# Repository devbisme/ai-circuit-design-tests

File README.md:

# ai-circuit-design-tests

There are now many [AI tools](https://devbisme.github.io/RepoRecon/?topic=kicad_ai&filter=&sort=pushed:desc) that claim to automate KiCad.
Some may work, many may not; it's hard to tell since example designs are either non-existent, show only partial results, or
are very simple (e.g. resistor dividers).

I'm going to try some of these AI tools to see how they perform.
This repo is the test bench. Each top-level subdirectory holds the artifacts of one tool
being exercised on a real design problem, plus an evaluation of what came out and what it
cost.

The tools that were tested fall into the following classes:

- **Generators** take a design prompt and produce a design: specs, BOM, schematics,
  netlists, and sometimes a board.
- **Analyzers** take an existing KiCad design and produce a report: design review findings,
  ERC/DRC/DFM checks, simulations, sourcing, etc. They don't create a design of their own,
  so they are run on a design produced by one of the generators tested here.
- **Hybrids** can both generate and analyze designs. They are tested in both roles: one run
  analyzes an existing design, and another creates a design from a prompt.

Because of this, the results and the directory layout differ between the classes.
A generator's output is judged by whether the design is correct and complete; an analyzer's
output is judged by whether its findings are real, relevant, and not missing anything important.

Note that I have not validated any of these designs for correctness.
I will report the results of my validation in each tool's directory when I'm done.
Please feel free to report any of your own evaluations here as an issue on this repo.

**If you are interested in trying any of these tools,**
the most important files to read are:

* `setup.md` which describes how to install the tool,

* `claude_transcript.txt` (in each run directory) which shows the interactions between the
  user and Claude when using the tool.

For a quick look at what a run produced, start with its `executive_summary.md`.

## Tools tested

| Directory | Tool | Class |
|---|---|---|
| [`skidl-skills-tests/`](skidl-skills-tests/) | [skidl-skills](https://github.com/devbisme/skidl-skills) | Generator |
| [`konnect-tests/`](konnect-tests/) | [Konnect](https://github.com/mixelpixx/Konnect) | Hybrid |
| [`copperhead-tests/`](copperhead-tests/) | [Copperhead](https://github.com/copperheadhq/copperhead) | Generator |
| [`kicad-happy-tests/`](kicad-happy-tests/) | [kicad-happy](https://github.com/aklofas/kicad-happy) | Analyzer |
| [`kicad-mcp-server-tests/`](kicad-mcp-server-tests/) | [kicad-mcp-server](https://github.com/Seeed-Studio/kicad-mcp-server) | Hybrid |
| [`kicad-mcp-pro-tests/`](kicad-mcp-pro-tests/) | [kicad-mcp-pro](https://github.com/oaslananka/kicad-mcp-pro) | Hybrid |
| [`eda-agent-tests/`](eda-agent-tests/) | [eda-agent](https://github.com/salitronic/eda-agent) | Hybrid |
| [`kicad-ai-assistant-tests/`](kicad-ai-assistant-tests/) | [KiCad-AI-Assistant](https://github.com/paul356/KiCad-AI-Assistant) | Hybrid |
| [`kicad-harness-tests/`](kicad-harness-tests/) | [kicad-harness](https://github.com/zxkmm/kicad-harness) | Hybrid |
| [`boardforge-tests/`](boardforge-tests/) | [boardforge](https://github.com/devbisme/boardforge) | Generator |
| [`null-tests/`](null-tests/) | None: Claude Code (Opus 5.5) with no KiCad-specific MCP servers, skills or plugins; a baseline | Hybrid |

Each generator's `README.md` describes the tool, why it was chosen, the prompt(s) it was given,
a cross-run comparison, and an evaluation of cost, runtime and quality of results.
Each analyzer's directory holds a copy of the design it analyzed (and notes where it came from),
the reports the tool produced, and an evaluation of the findings, cost and runtime.
A hybrid's directory has one of each kind of run.

## Comparable runs

Two sets of runs share their inputs, so their results can be compared across tools.

**Same design prompt.** These runs got the dual-ADC requirements prompt (dual-channel,
±10 V, 10 MS/s, 12-bit, ≥0.1 s of capture, USB 2.0). Each was told to start from a blank
slate.

| Run | Tool's role | Reached (as reported by the session) | Equiv. API cost |
|---|---|---|---|
| [Konnect 2](konnect-tests/dual-adc-usb-2/) | Design tool | Routed 4-layer board, DRC clean | $61.12 |
| [kicad-mcp-server 2](kicad-mcp-server-tests/dual-adc-usb-2/) | Design tool, gaps filled by scripts | Routed 4-layer board, 4 DRC errors (stock USB-C footprint) | $16.93 |
| [kicad-happy 2](kicad-happy-tests/dual-adc-usb-2/) | Reviewer; Claude built the design with SKiDL and scripts | Routed 4-layer board, 0 ERC/DRC errors | $29.37 |
| [kicad-mcp-pro 2](kicad-mcp-pro-tests/dual-adc-usb-2/) | Design tool, gaps filled by scripts | Routed 4-layer board, 0 ERC/DRC errors | $19.42 |
| [eda-agent 2](eda-agent-tests/dual-adc-usb-2/) | Design tool (KiCad backend), gaps filled by scripts | Routed 4-layer board, 0 ERC/DRC errors | $18.47 |
| [KiCad-AI-Assistant 2](kicad-ai-assistant-tests/dual-adc-usb-2/) | Design tool (kcaa MCP server), gaps filled by scripts | Routed 4-layer board, 0 ERC/DRC errors | $19.38 |
| [kicad-harness 2](kicad-harness-tests/generate-1/) | Checks, lookups and renders (`kh` CLI); Claude's scripts wrote the schematic, placed and finished routing | Routed 4-layer board, 0 ERC/DRC errors | $10.87 |
| [null test 2](null-tests/generate-1/) | No tool (baseline): Claude used SKiDL and schematizer for the schematic, its own `pcbnew` scripts and Freerouting for the board | Routed 4-layer board, 0 ERC/DRC errors; signals routed through the In1 GND plane | $11.16 |
| [boardforge 1](boardforge-tests/generate-1/) | Design pipeline: `/new-circuit` agents wrote the SKiDL design, the `boardforge` CLI made the schematic, placed, routed and wrote fab files | Routed 4-layer board, 0 ERC/DRC errors, review and release gates PASS; CPL dropped 80 parts (tool bug, fixed by hand) | $23.89 |

These nine runs used the prompt with an added line giving the KiCad 10 executable's path.
The version without that line was used for SKiDL Skills runs 5–9, Konnect run 1 and
Copperhead run 1.

**Same input design.** These runs analyzed the KiCad project from Konnect run 2.

| Run | Equiv. API cost |
|---|---|
| [kicad-happy 1](kicad-happy-tests/dual-adc-usb-1/) | $1.92 |
| [kicad-mcp-server 1](kicad-mcp-server-tests/dual-adc-usb-1/) | $2.05 |
| [kicad-mcp-pro 1](kicad-mcp-pro-tests/dual-adc-usb-1/) | $2.24 |
| [eda-agent 1](eda-agent-tests/dual-adc-usb-1/) | $3.43 |
| [KiCad-AI-Assistant 1](kicad-ai-assistant-tests/dual-adc-usb-1/) | $3.71 |
| [kicad-harness 1](kicad-harness-tests/analyze-1/) | $3.02 |
| [null test 1](null-tests/analyze-1/) | $1.91 |

The prompts differed between these runs, so they did not ask for exactly the same things.
Each tool's `README.md` lists its prompts and findings.

None of these designs or findings has been validated yet.

## Layout

This is the layout for generators. Analyzers follow it loosely: the KiCad files in their
directories are inputs copied from a generator's run, not outputs, and the main output is
the analysis report.

```
ai-circuit-design-tests/
├── README.md                 <- this file
└── <tool-name>-tests/        <- one directory per AI tool under test
    ├── README.md             <- the tool, the design prompt, cross-run comparison, evaluation
    ├── setup.md              <- how the tool was installed and configured
    └── <design>-<run#>/      <- one directory per run
        ├── README.md         <- (some runs) what was run, what came out, evaluation, cost
        ├── *-prompt.txt          <- the verbatim prompt given to the tool
        ├── claude_transcript.txt <- transcript of interactions between the user and Claude
        ├── claude_cost.txt       <- token usage and equivalent API cost
        ├── executive_summary.md  <- overall description of the design process, results, risks.
        └── ...                   <- everything the tool produced
```

One run per directory, never overwritten. Runs are numbered so a prompt change or a tool
change can be compared against the previous attempt on the same design. Where possible,
different tools are given the same design prompt so their results can be compared.

## What each run should capture

- The verbatim prompt (`*-prompt.txt`).
- Everything the tool wrote — specs, architecture docs, BOM, datasheets, code, ERC/DRC logs,
  netlists, schematics, boards — left where the tool put it.
- The session transcript (`claude_transcript.txt`, via `/export`), when the tool is interactive.
- Cost. `claude_cost.txt` holds token counts and the equivalent first-party API price. It
  comes from `session_cost.py`, which sums usage from the main transcript **and** the
  subagent transcripts; the main file alone misses most of the spend. Save it at the end of
  the session, before doing any unrelated work in the same session, or the total will
  include that work too.

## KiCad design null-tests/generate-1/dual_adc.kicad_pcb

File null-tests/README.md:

# Null test — tests

## Tool under test

None. This is a **null test**: Claude Code with Claude Opus 5.5 and no KiCad-specific MCP
server, skill, plugin, subagent or memory. It is the baseline for the other tools in this
repo: their results can be read against what Claude does with only its built-in tools.

What it has to work with:

- Claude Code's built-in tools: Bash, Read, Write, Edit, web search and fetch.
- KiCad 10's own programs: `kicad-cli` (ERC, DRC, netlist, Gerber, drill, BOM, position,
  PDF/SVG export) and the `pcbnew` Python module in KiCad 10's bundled Python 3.11.
- Whatever else it finds on the machine. That includes KiCad-specific Python packages and
  CLIs that were not removed (`skidl`, `schematizer`, `kipart`, `kinet2pcb`, `kicad-skip`; see [`setup.md`](setup.md)).

Claude can both review and create designs, so this is tested as a **hybrid**, like
[kicad-harness](../kicad-harness-tests/) and [KiCad-AI-Assistant](../kicad-ai-assistant-tests/).
Setup, including what has to be turned off before each run, is in [`setup.md`](setup.md).

- **Version:** n/a (no tool).
- **Model:** Claude Opus 5.5 on a Claude Pro plan (both runs).
- **Claude Code version:** v2.1.301 (both runs).
- **Backend:** KiCad 10.0.4 (`~/bin/kicad10-root`: `kicad-cli` and the bundled Python 3.11
  `pcbnew`).

## Why this tool

*Draft:* every other tool here is judged by what it produced, but not against what Claude
would have produced without it. The null test supplies that comparison: the same two prompts,
the same model and the same KiCad 10, with none of the tools.

## Runs

| Run | What it tests | Prompts | Outcome | Equiv. API cost | Time |
|---|---|---|---|---|---|
| [`analyze-1`](analyze-1/) | **Analysis** and JLCPCB fab outputs for an existing design (Konnect run 2) | 1 (multi-part, [`analysis_prompt.txt`](analyze-1/analysis_prompt.txt)) | ERC 0 errors, DRC 0 errors; 15 ranked findings; Gerbers, BOM, CPL, PNG. Its top finding (clamp diodes miswired) is probably a false positive | $1.91 | ~6 min |
| [`generate-1`](generate-1/) | A **full design** from the dual-ADC requirements | 1, plus 1 "are you done?" while Freerouting ran ([`design_prompt.txt`](generate-1/design_prompt.txt)) | 10-sub-sheet schematic and routed 4-layer board. ERC 0 errors, DRC 0 errors / 0 unconnected / 0 parity. Signals routed through the In1 GND plane | $11.16 | ~2 h 42 min wall clock (~1 h 17 min of Claude working time) |

Each run directory has an `executive_summary.md`; start there. Costs are the equivalent
first-party API price of the tokens used (`claude_cost.txt`), not what the Pro subscription
billed. The findings in both runs have not yet been validated by hand.

### analyze-1: analyzer on an existing design

The input is the KiCad project produced by
[Konnect run 2](../konnect-tests/dual-adc-usb-2/): a 4-layer, 140 × 90 mm dual-channel 12-bit,
10 MS/s ADC board with a USB 2.0 interface (LTC2290 ADC, iCE40HX4K FPGA, SDRAM, FT2232H).
The `.kicad_*` files are unchanged copies. The other tools' analysis runs used the same
design.

Prompt: `do what aanalysis_prompt.txt says to do.` (typo as typed;
[`analysis_prompt.txt`](analyze-1/analysis_prompt.txt) asks for a design review, JLCPCB
Gerbers, BOM and CPL, a dark-gray PCB PNG and an executive summary.)

Quick look:

- **Checks:** `kicad-cli` ERC gave 0 errors, 155 library-mismatch warnings and 2 benign
  pin-type warnings. DRC with schematic parity gave 0 errors and 0 unconnected; the warnings
  are library mismatches and silkscreen.
- **Review method:** a netlist export and a per-IC pin-to-net dump (`out/pinmap.txt`) checked
  against datasheet knowledge, plus a script that parsed the `.kicad_pcb` for stackup, plane
  fills, track and via sizes and decap-to-pin distances (`out/pcbstat.txt`). **No datasheets
  were fetched**; part-behaviour claims are from memory and labelled *(datasheet recall)*.
- **Findings (15, ranked High/Medium/Low):**
  - High: BAV199DW input clamps wired so they do nothing; decoupling caps 6–22 mm from their
    pins on the ADC, FPGA, SDRAM, FT2232H and charge pump; the 10 MHz oscillator runs from
    the PWREN#-gated +3V0 rail, so the FPGA has no clock until USB enumerates.
  - Medium: FT2232H channel B (flash/FPGA programming) unusable while channel A is in sync
    FIFO; USB D+/D− not impedance-controlled; the unpowered ADC is back-powered through its
    outputs; the LM27762 charge pump sits between the two AFE channels; likely over the USB
    unconfigured/suspend current limits.
  - Low: single-pole anti-alias filter, shared ADC OVDD/VDD rail, no vias in the ADA4817
    pads, unprotected header GPIO, BNC overhang, silkscreen, library/field housekeeping.
  - A list of items that were checked and found correct (divider compensation, full-scale
    range, FDA common mode, regulator setpoints, LTC2290 configuration, FT2232H support
    parts, iCE40 configuration, SDRAM pinout, planes).
- **The clamp finding is probably wrong.** [eda-agent 1](../eda-agent-tests/dual-adc-usb-1/)
  and [KiCad-AI-Assistant 1](../kicad-ai-assistant-tests/dual-adc-usb-1/) downloaded the
  Diodes BAV199DW datasheet (ds30417) and found that KiCad's pin names are misleading but the
  real package clamps correctly. This run read only the KiCad pin names. It did add "verify
  that the symbol's pin numbering matches the real BAV199DW package", but still ranked the
  finding first. Not yet checked by hand.
- **Outputs:** Gerbers and Excellon drill from `kicad-cli` (Protel extensions, zipped), a
  JLCPCB-format BOM (LCSC column empty) and CPL in `fab/`, and `dual_adc_usb_pcb.png` at
  400 dpi on #3a3a3a. Intermediate reports are in `out/`.
- **Didn't read anything outside the run directory**, as far as the transcript shows.

### generate-1: full design

The prompt is [`design_prompt.txt`](generate-1/design_prompt.txt), identical to the one used
for the other tools' design runs (the version with the KiCad 10 path line).

Prompts, in sequence in one session:

```
create the design described in design_prompt.txt
```
```
are you done?
```

The session ended its turn several times while Freerouting ran in the background, and the
router's completion notices re-started it. Once it ended its turn saying it was waiting on a
second routing pass over the routed board; after about 17 minutes, "are you done?" got it to
check. That pass had gone from 4 unrouted to 60, so Claude stopped it and went back to the first pass's board.

Quick look:

- **Design:**
  - Signal path: BNC → 1 MΩ‖20 pF attenuator with its bottom leg on a REF3020 2.048 V
    reference → BAV199 clamps → OPA356 buffer → THS4521 FDA (other input gets a buffered copy
    of the attenuator's rest voltage) → RC → LTC2290. ±10.09 V full scale, ~4.4 MHz
    bandwidth, 2nd-order anti-aliasing.
  - Capture and link: iCE40HX4K-TQ144 with an 8 MB IS42S16400J SDRAM (0.2 s at full rate,
    twice the requirement); FT232H in sync-245 FIFO mode; SPI config flash programmed from a
    2×4 header.
  - Clock: 10 MHz XO on the 3.0 V analog rail, buffered to the ADC and an FPGA global clock
    pin.
  - Power: USB-B, ~260 mA estimated, so USB-C wasn't needed. TPS62160 buck (3.3 V), AP2112
    (1.2 V), LP5907 (4.5 V analog, 3.0 V ADC/clock). Single supply; no negative rail.
  - The ten decisions (options → choice) are in the executive summary.
- **Schematic:** written in SKiDL (`dual_adc.py`) and drawn by schematizer as a root plus 10
  sub-sheets.
  - The `kicad-cli` netlist of the drawn schematic matches the SKiDL netlist
    (`compare_nets.py`, 0 differing nets). That check caught a schematizer bug that drew a
    PLL-filter R on top of its C and shorted +1V2 to GND.
  - KiCad ERC: 0 errors, 435 warnings (off-grid wire ends, library-copy mismatches, 2
    intentional flash WP/HOLD ties).
- **PCB:** 140 × 95 mm, 4 layers (In1 GND plane), 182 footprints, 339 vias.
  - Claude's `make_pcb.py` (KiCad 10 `pcbnew`) loaded footprints, assigned nets, did
    rule-based placement, the outline and the In1 plane. `route.py` handled DSN export,
    SES import, pours and copying symbol fields onto footprints.
  - Freerouting 2.4.1 took four full runs (10–30 min each). Run 3 left 0 unrouted and is the
    delivered board. Run 4, with In1 reserved for GND, left 4 signals and ~19 GND pads
    unconnected and was rejected.
  - DRC (KiCad 10, with schematic parity): 0 errors, 0 unconnected, 0 parity, 30 warnings.
    Track and hole minimums were relaxed to 0.10 mm / 0.25 mm for router neck-downs and the
    buck's thermal vias.
- **Not ready for fab:**
  - Freerouting put 81 nets (~1.7 m of track) on the In1 GND plane, including under the
    ADC. The summary calls this the biggest layout weakness.
  - USB D+/D− not routed as a 90 Ω pair; ~260 mA draw before enumeration (limit 100 mA);
    fixed (not trimmable) attenuator compensation.
  - No datasheets were re-read; LTC2290, FT232H, THS4521, iCE40, TPS62160 and REF3020
    details are from memory and labelled that way. Not simulated.
  - No Gerbers or drill files (the prompt didn't ask for them). No FPGA gateware or host
    software.
- **Problems hit:** schematizer crashed on footprint-only parts, needed `auto_stub=True` to
  route, and overlapped two parts (above); the OPA356 SOIC symbol's hidden NC pins landed on
  nets; `pcbnew`'s `board.Save()` overwrites `.kicad_pro` with default rules, so
  `write_project.py` re-applies them after every save.

### Was the null test clean?

Not entirely; both points come from the end of the generate-1 transcript and from
`setup.md`.

- **KiCad-specific packages were used.** generate-1 built the schematic with SKiDL and
  schematizer, which `setup.md` left installed. Claude also read schematizer's README and
  source to work around its bugs. analyze-1 used only `kicad-cli` and its own Python.
- **generate-1 read the repo-root README.** Asked afterwards, Claude said it read the root
  `README.md`, including the "Comparable runs" table, and that the table "is why I aimed for
  a routed, DRC-clean 4-layer board instead of stopping at a schematic". It said it chose the
  architecture before opening the README and copied no design details, but couldn't rule out
  an influence on later choices. It read none of the other tools' design files or reports.
  For future runs, moving that table aside or blocking reads above `null-tests/` would close
  this leak.

### Comparison of the two runs, and with the other tools

- **Cost:** analyze-1 ($1.91) is the cheapest of the analysis runs on this design
  ($1.92–$3.71). generate-1 ($11.16) is close to kicad-harness 2 ($10.87), the cheapest of
  the tool-assisted design runs ($10.87–$61.12).
- **Datasheets:** neither run fetched a datasheet. The tools whose runs did (eda-agent and
  KiCad-AI-Assistant in their analysis runs) avoided the clamp false positive. Fetching
  datasheets isn't something those tools add; it is a choice the session made.
- **Gap filling:** generate-1 looks like the tool-assisted design runs from the other side:
  they also ended with Claude-written scripts for placement and routing, plus Freerouting.
  The difference is the schematic, which here came from SKiDL and schematizer rather than
  the tool under test.
- **Same weak spots as the other design runs:** USB pair impedance, unconfigured USB current,
  silkscreen, and part details from memory.

## Layout

```
null-tests/
├── README.md                   <- this file
├── setup.md                    <- what was turned off for the runs, and why
├── analyze-1/                  <- run 1: analysis of the Konnect run-2 design
│   ├── executive_summary.md    <- start here
│   ├── analysis_prompt.txt     <- the prompt (unchanged copy of the repo-root one)
│   ├── CLAUDE.md               <- empty project memory file
│   ├── claude_transcript.txt   <- the session
│   ├── claude_cost.txt         <- token usage and equivalent API cost
│   ├── session_cost.py         <- script that produced claude_cost.txt
│   ├── dual_adc_usb.kicad_pro, .kicad_sch, .kicad_pcb, .kicad_prl, .kicad_dru
│   ├── adc, afe_a, afe_b, fpga, power, usb .kicad_sch
│   ├── dual_adc_usb_pcb.png    <- PCB render on a dark-gray background
│   ├── fab/                    <- Gerber zip, unzipped gerbers, JLCPCB BOM and CPL
│   └── out/                    <- ERC/DRC JSON, netlist, pin map, PCB stats, raw BOM/pos, SVG
└── generate-1/                 <- run 2: full design from the dual-ADC prompt
    ├── executive_summary.md    <- start here
    ├── design_prompt.txt       <- the design prompt
    ├── CLAUDE.md               <- empty project memory file
    ├── claude_transcript.txt   <- the session
    ├── claude_cost.txt         <- token usage and equivalent API cost
    ├── session_cost.py         <- script that produced claude_cost.txt
    ├── dual_adc.py             <- SKiDL description of the circuit (source of truth)
    ├── dual_adc.kicad_pro, .kicad_sch, .kicad_pcb, .kicad_prl
    ├── dual_adc_*.kicad_sch    <- 10 sub-sheets drawn by schematizer
    ├── dual_adc_schematic.pdf, dual_adc_top.png, dual_adc_bom.csv
    ├── dual_adc.net, dual_adc_sch.net  <- SKiDL netlist / netlist of the drawn schematic
    ├── dual_adc.xml, dual_adc.erc, dual_adc.log  <- SKiDL outputs
    ├── erc.rpt, drc.rpt        <- final KiCad 10 ERC/DRC reports
    ├── dual_adc.dsn, dual_adc.ses, freerouting.log  <- Freerouting input/output
    ├── fix_sch.py              <- schematic post-fix (PWR_FLAG footprints)
    ├── compare_nets.py         <- netlist-vs-netlist check
    ├── make_pcb.py             <- footprints, nets, placement, outline, In1 plane
    ├── route.py                <- DSN export, SES import, pours, symbol-field relink
    ├── finish_board.py         <- starved-thermal fixes, board-only holes, zone refill
    └── write_project.py        <- writes .kicad_pro design rules and net classes
```

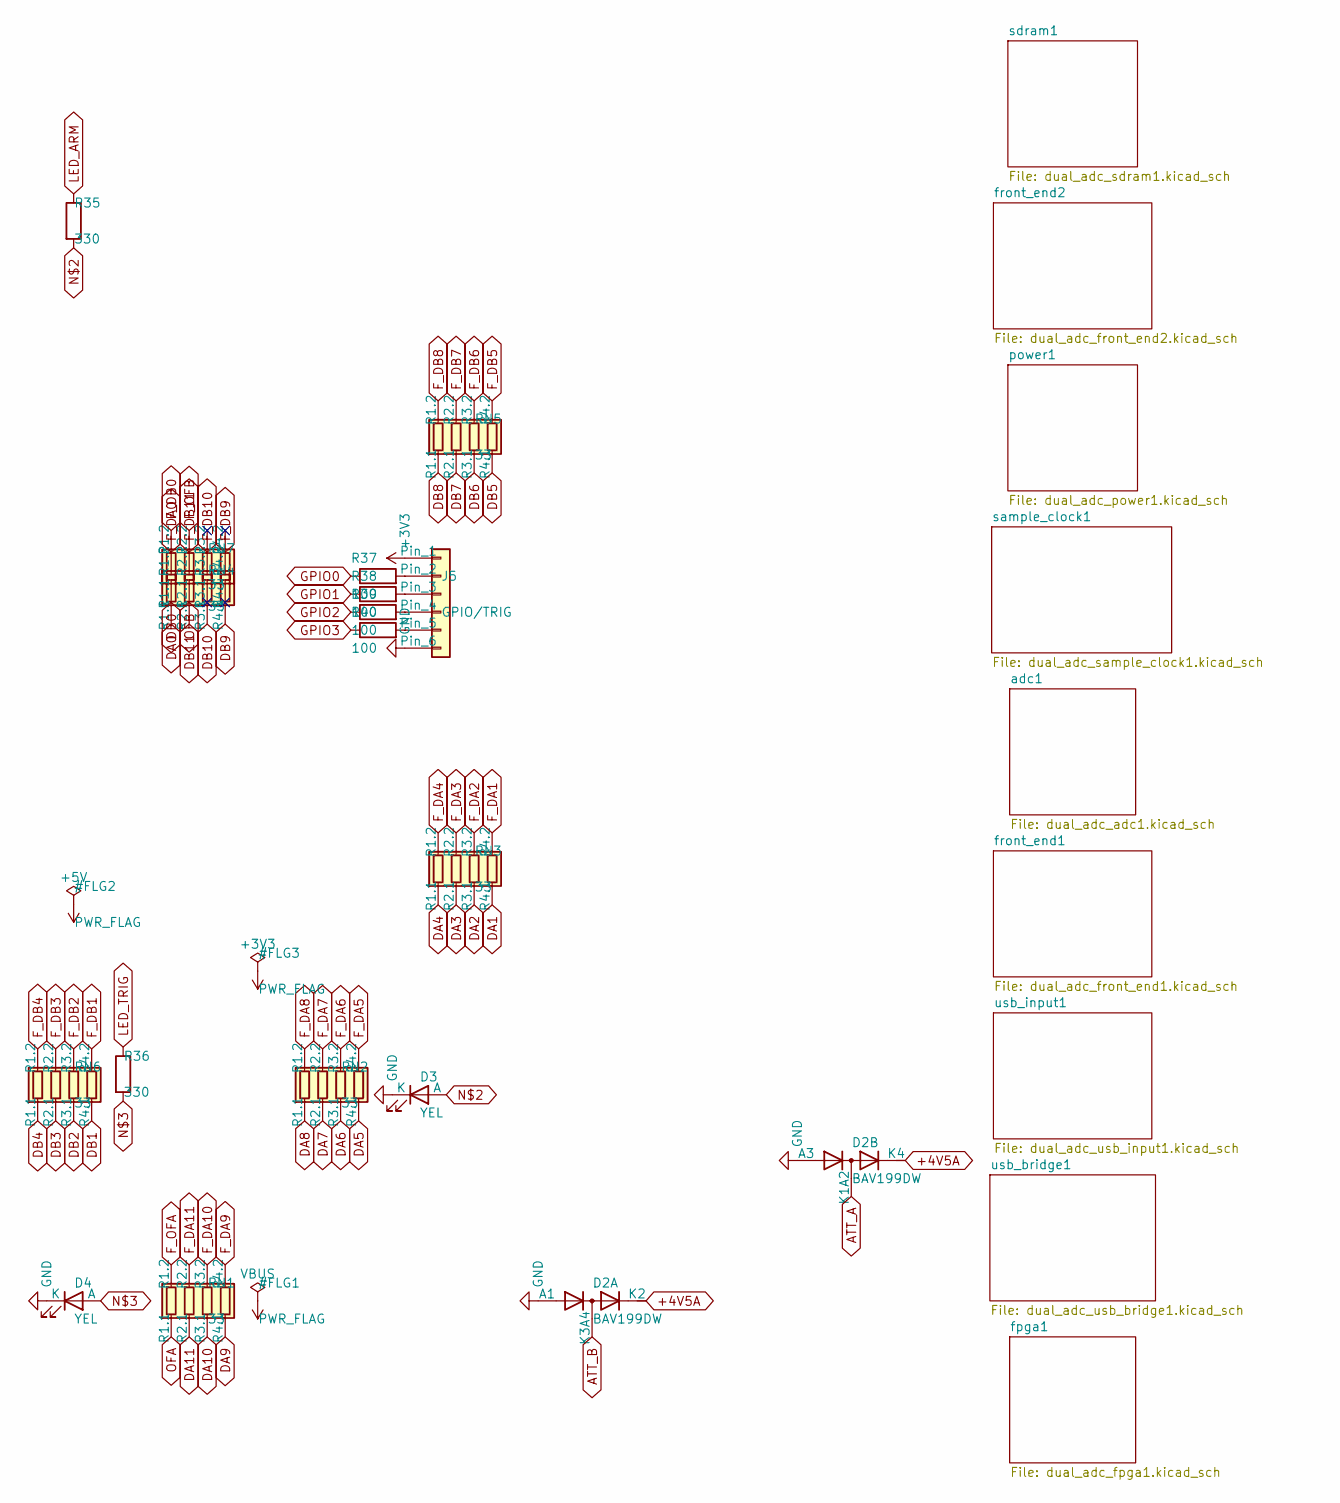
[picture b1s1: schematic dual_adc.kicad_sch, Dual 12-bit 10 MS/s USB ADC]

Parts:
D2: BAV199DW; SOT-363_SC-70-6
D3, D4: YEL; LED_0603_1608Metric
J5: GPIO/TRIG; PinHeader_1x06_P2.54mm_Vertical
R35, R36: 330; R_0603_1608Metric
R37, R38, R39, R40: 100; R_0603_1608Metric
RN1, RN2, RN3, RN4, RN5, RN6, RN7: 33; R_Array_Convex_4x0603

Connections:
+3V3: J5.1; also elsewhere on the board
+4V5A: D2.2 (K2), D2.5 (K4); also elsewhere on the board
ATT_A: D2.3 (K1A2); also elsewhere on the board
ATT_B: D2.6 (K3A4); also elsewhere on the board
DA0: RN4.1 (R1.1); also elsewhere on the board
DA1: RN3.4 (R4.1); also elsewhere on the board
DA2: RN3.3 (R3.1); also elsewhere on the board
DA3: RN3.2 (R2.1); also elsewhere on the board
DA4: RN3.1 (R1.1); also elsewhere on the board
DA5: RN2.4 (R4.1); also elsewhere on the board
DA6: RN2.3 (R3.1); also elsewhere on the board
DA7: RN2.2 (R2.1); also elsewhere on the board
DA8: RN2.1 (R1.1); also elsewhere on the board
DA9: RN1.4 (R4.1); also elsewhere on the board
DA10: RN1.3 (R3.1); also elsewhere on the board
DA11: RN1.2 (R2.1); also elsewhere on the board
DB0: RN7.1 (R1.1); also elsewhere on the board
DB1: RN6.4 (R4.1); also elsewhere on the board
DB2: RN6.3 (R3.1); also elsewhere on the board
DB3: RN6.2 (R2.1); also elsewhere on the board
DB4: RN6.1 (R1.1); also elsewhere on the board
DB5: RN5.4 (R4.1); also elsewhere on the board
DB6: RN5.3 (R3.1); also elsewhere on the board
DB7: RN5.2 (R2.1); also elsewhere on the board
DB8: RN5.1 (R1.1); also elsewhere on the board
DB9: RN4.4 (R4.1); also elsewhere on the board
DB10: RN4.3 (R3.1); also elsewhere on the board
DB11: RN4.2 (R2.1); also elsewhere on the board
F_DA0: RN4.8 (R1.2); also elsewhere on the board
F_DA1: RN3.5 (R4.2); also elsewhere on the board
F_DA2: RN3.6 (R3.2); also elsewhere on the board
F_DA3: RN3.7 (R2.2); also elsewhere on the board
F_DA4: RN3.8 (R1.2); also elsewhere on the board
F_DA5: RN2.5 (R4.2); also elsewhere on the board
F_DA6: RN2.6 (R3.2); also elsewhere on the board
F_DA7: RN2.7 (R2.2); also elsewhere on the board
F_DA8: RN2.8 (R1.2); also elsewhere on the board
F_DA9: RN1.5 (R4.2); also elsewhere on the board
F_DA10: RN1.6 (R3.2); also elsewhere on the board
F_DA11: RN1.7 (R2.2); also elsewhere on the board
F_DB0: RN7.8 (R1.2); also elsewhere on the board
F_DB1: RN6.5 (R4.2); also elsewhere on the board
F_DB2: RN6.6 (R3.2); also elsewhere on the board
F_DB3: RN6.7 (R2.2); also elsewhere on the board
F_DB4: RN6.8 (R1.2); also elsewhere on the board
F_DB5: RN5.5 (R4.2); also elsewhere on the board
F_DB6: RN5.6 (R3.2); also elsewhere on the board
F_DB7: RN5.7 (R2.2); also elsewhere on the board
F_DB8: RN5.8 (R1.2); also elsewhere on the board
F_DB9: RN4.5 (R4.2); also elsewhere on the board
F_DB10: RN4.6 (R3.2); also elsewhere on the board
F_DB11: RN4.7 (R2.2); also elsewhere on the board
F_OFA: RN1.8 (R1.2); also elsewhere on the board
F_OFB: RN7.7 (R2.2); also elsewhere on the board
GND: D2.1 (A1), D2.4 (A3), D3.1 (K), D4.1 (K), J5.6; also elsewhere on the board
GPIO0: R37.1; also elsewhere on the board
GPIO1: R38.1; also elsewhere on the board
GPIO2: R39.1; also elsewhere on the board
GPIO3: R40.1; also elsewhere on the board
LED_ARM: R35.1; also elsewhere on the board
LED_TRIG: R36.1; also elsewhere on the board
unnamed: D3.2 (A), R35.2
unnamed: D4.2 (A), R36.2
unnamed: J5.2, R37.2
unnamed: J5.3, R38.2
unnamed: J5.4, R39.2
unnamed: J5.5, R40.2
OFA: RN1.1 (R1.1); also elsewhere on the board
OFB: RN7.2 (R2.1); also elsewhere on the board

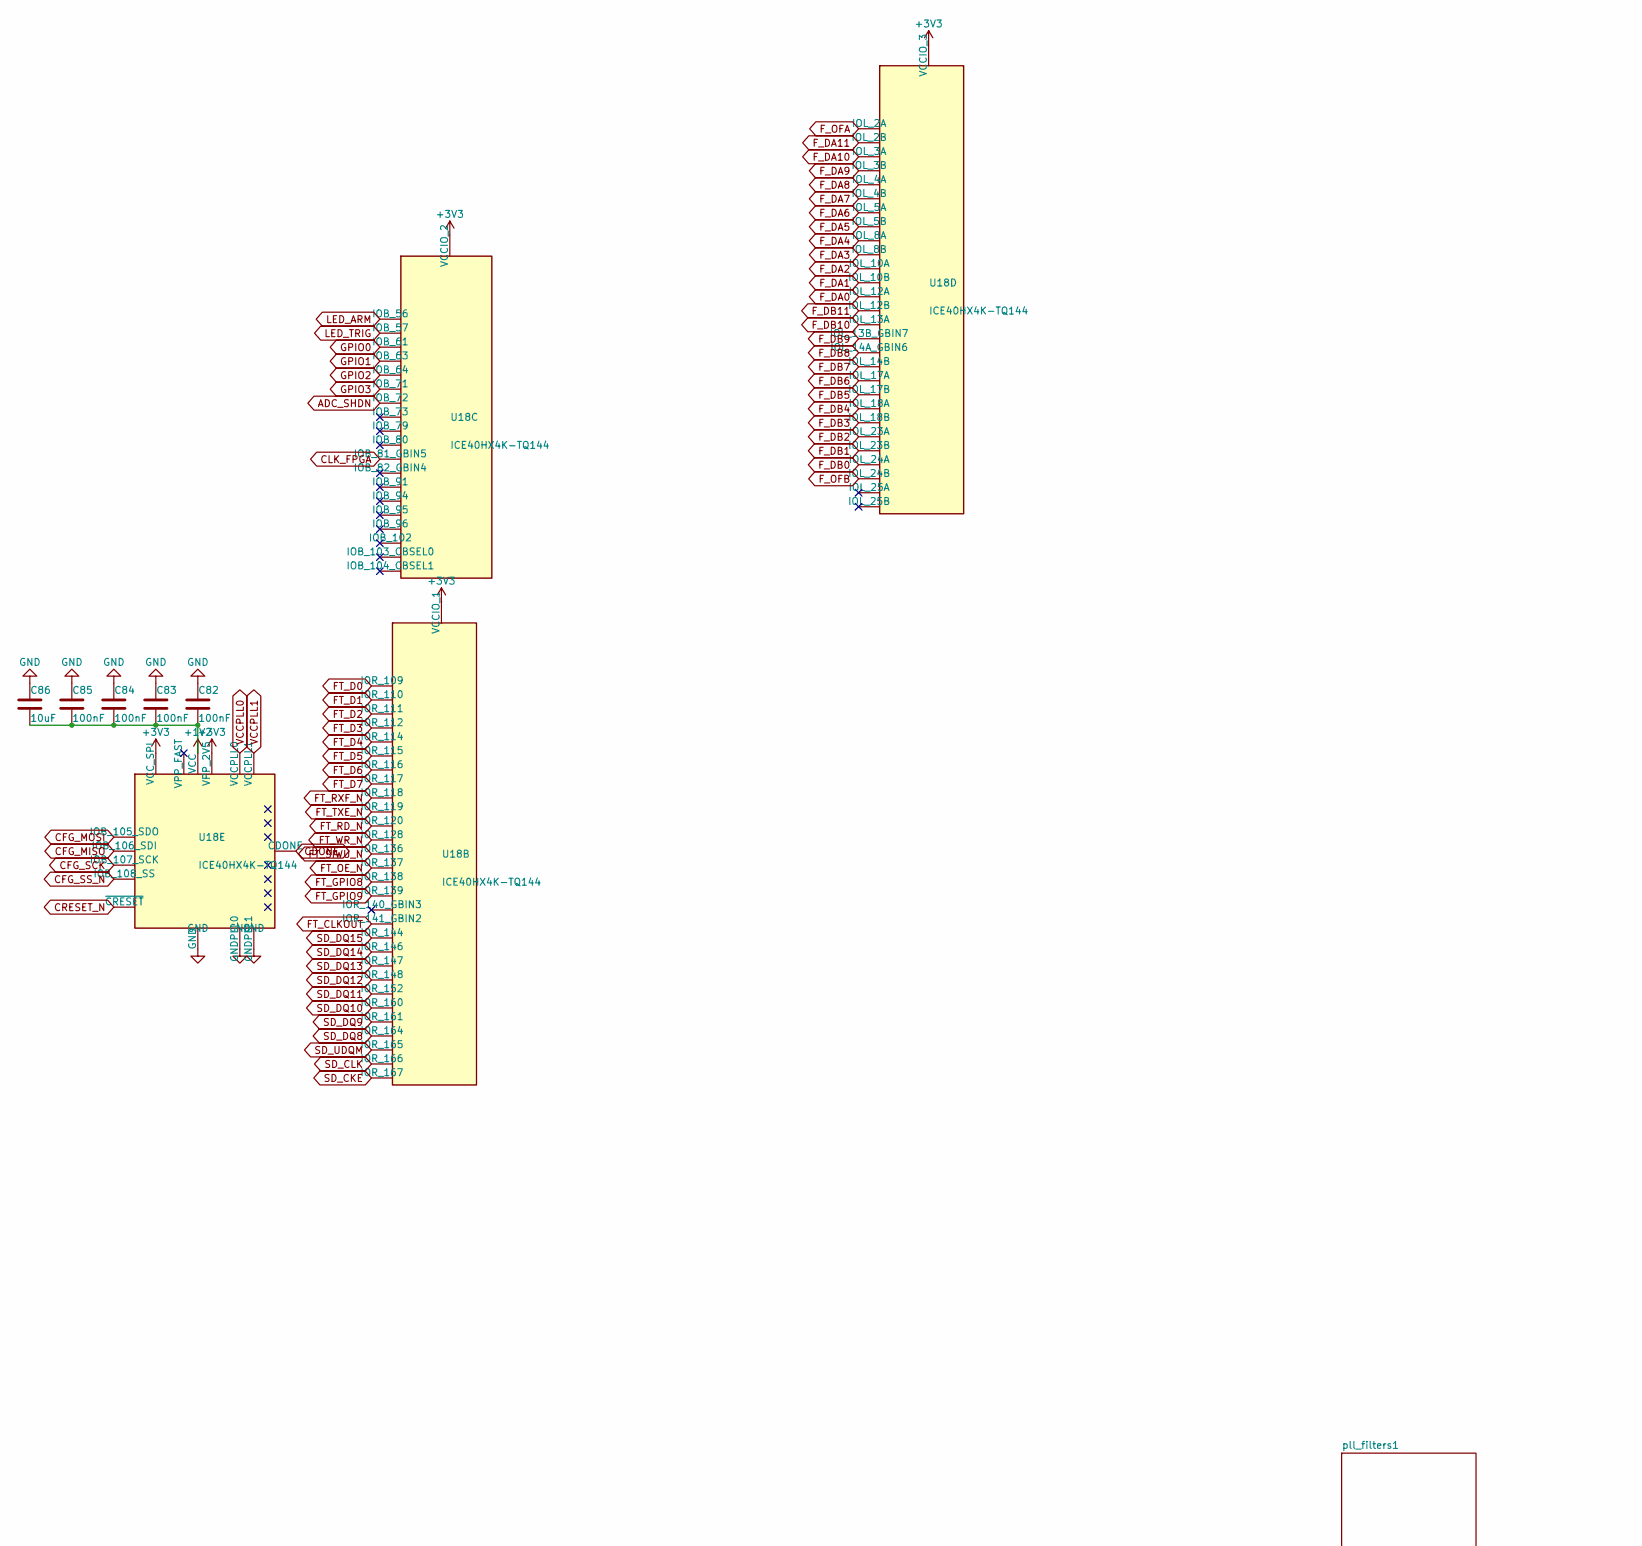
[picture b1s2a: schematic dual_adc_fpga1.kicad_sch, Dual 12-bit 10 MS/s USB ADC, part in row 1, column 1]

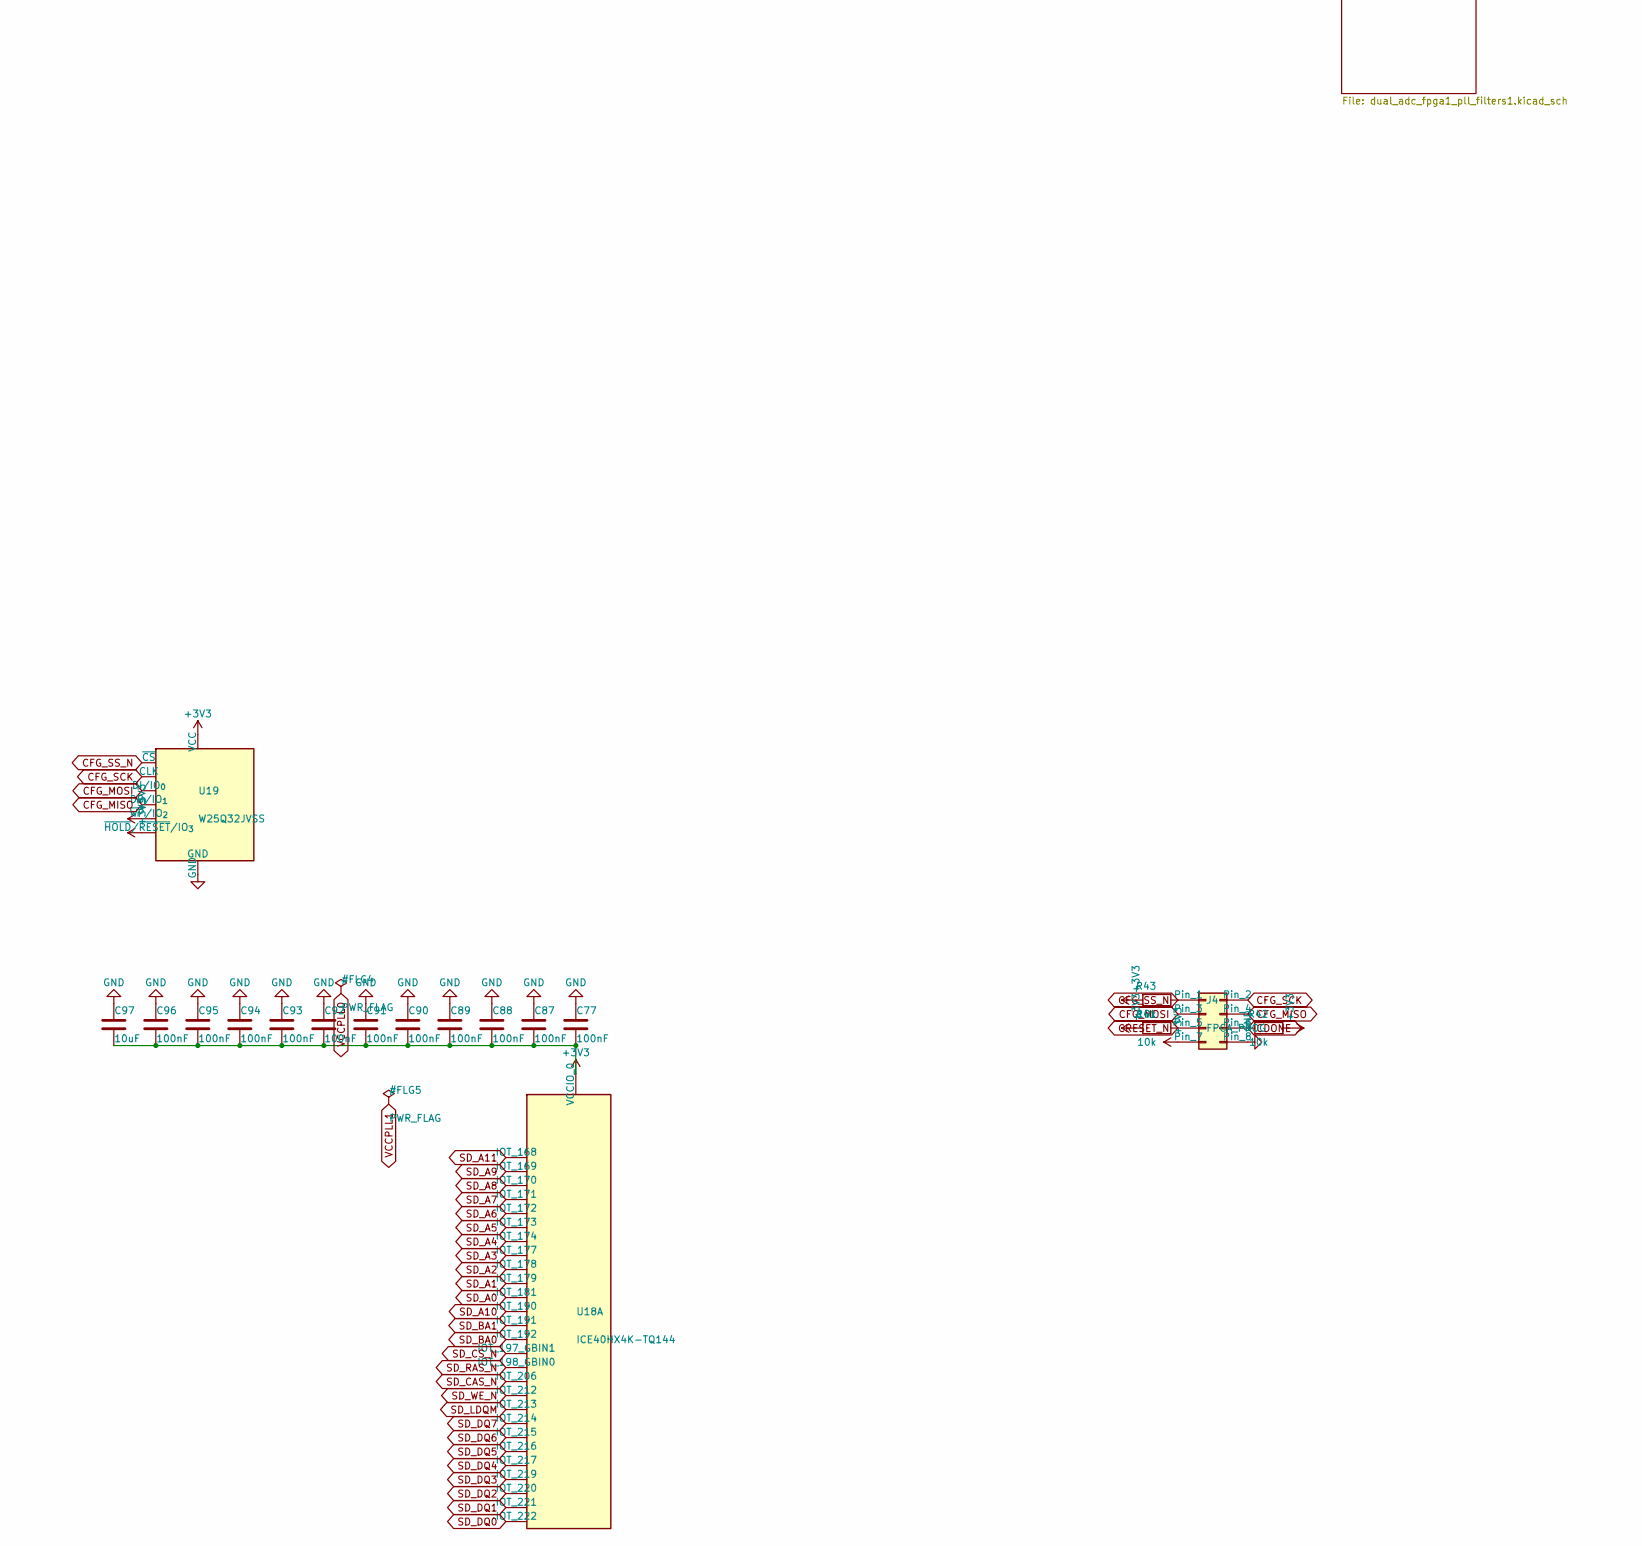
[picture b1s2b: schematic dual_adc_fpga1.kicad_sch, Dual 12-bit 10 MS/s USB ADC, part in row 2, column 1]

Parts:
C77, C82, C83, C84, C85, C87, C88, C89, C90, C91, C92, C93, C94, C95, C96: 100nF; C_0402_1005Metric
C86, C97: 10uF; C_0805_2012Metric
J4: FPGA_PROG; PinHeader_2x04_P2.54mm_Vertical
R41, R42, R43: 10k; R_0603_1608Metric
U18: ICE40HX4K-TQ144; TQFP-144_20x20mm_P0.5mm
U19: W25Q32JVSS; SOIC-8_5.3x5.3mm_P1.27mm

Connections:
+1V2: C82.1, C83.1, C84.1, C85.1, C86.1, U18.27 (VCC), U18.40 (VCC), U18.92 (VCC), U18.111 (VCC); also elsewhere on the board
+3V3: C77.1, C87.1, C88.1, C89.1, C90.1, C91.1, C92.1, C93.1, C94.1, C95.1, C96.1, C97.1, J4.7, R41.2, R42.2, R43.2, U18.6 (VCCIO_3), U18.30 (VCCIO_3), U18.46 (VCCIO_2), U18.57 (VCCIO_2), U18.72 (VCC_SPI), U18.89 (VCCIO_1), U18.100 (VCCIO_1), U18.108 (VPP_2V5), U18.123 (VCCIO_0), U18.131 (VCCIO_0), U19.3 (~WP/IO_{2}), U19.7 (~HOLD/~RESET/IO_{3}), U19.8 (VCC); also elsewhere on the board
ADC_SHDN: U18.44 (IOB_72); also elsewhere on the board
CDONE: J4.6, R42.1, U18.65 (CDONE)
CFG_MISO: J4.4, U18.68 (IOB_106_SDI), U19.2 (DO/IO_{1})
CFG_MOSI: J4.3, U18.67 (IOB_105_SDO), U19.5 (DI/IO_{0})
CFG_SCK: J4.2, U18.70 (IOB_107_SCK), U19.6 (CLK)
CFG_SS_N: J4.1, R43.1, U18.71 (IOB_108_SS), U19.1 (~CS)
CRESET_N: J4.5, R41.1, U18.66 (~CRESET)
FT_CLKOUT: U18.94 (IOR_141_GBIN2); also elsewhere on the board
FT_D0: U18.73 (IOR_109); also elsewhere on the board
FT_D1: U18.74 (IOR_110); also elsewhere on the board
FT_D2: U18.75 (IOR_111); also elsewhere on the board
FT_D3: U18.76 (IOR_112); also elsewhere on the board
FT_D4: U18.78 (IOR_114); also elsewhere on the board
FT_D5: U18.79 (IOR_115); also elsewhere on the board
FT_D6: U18.80 (IOR_116); also elsewhere on the board
FT_D7: U18.81 (IOR_117); also elsewhere on the board
FT_GPIO8: U18.90 (IOR_138); also elsewhere on the board
FT_GPIO9: U18.91 (IOR_139); also elsewhere on the board
FT_OE_N: U18.88 (IOR_137); also elsewhere on the board
FT_RD_N: U18.84 (IOR_120); also elsewhere on the board
FT_RXF_N: U18.82 (IOR_118); also elsewhere on the board
FT_SIWU_N: U18.87 (IOR_136); also elsewhere on the board
FT_TXE_N: U18.83 (IOR_119); also elsewhere on the board
FT_WR_N: U18.85 (IOR_128); also elsewhere on the board
F_DA0: U18.17 (IOL_12A); also elsewhere on the board
F_DA1: U18.16 (IOL_10B); also elsewhere on the board
F_DA2: U18.15 (IOL_10A); also elsewhere on the board
F_DA3: U18.12 (IOL_8B); also elsewhere on the board
F_DA4: U18.11 (IOL_8A); also elsewhere on the board
F_DA5: U18.10 (IOL_5B); also elsewhere on the board
F_DA6: U18.9 (IOL_5A); also elsewhere on the board
F_DA7: U18.8 (IOL_4B); also elsewhere on the board
F_DA8: U18.7 (IOL_4A); also elsewhere on the board
F_DA9: U18.4 (IOL_3B); also elsewhere on the board
F_DA10: U18.3 (IOL_3A); also elsewhere on the board
F_DA11: U18.2 (IOL_2B); also elsewhere on the board
F_DB0: U18.31 (IOL_24A); also elsewhere on the board
F_DB1: U18.29 (IOL_23B); also elsewhere on the board
F_DB2: U18.28 (IOL_23A); also elsewhere on the board
F_DB3: U18.26 (IOL_18B); also elsewhere on the board
F_DB4: U18.25 (IOL_18A); also elsewhere on the board
F_DB5: U18.24 (IOL_17B); also elsewhere on the board
F_DB6: U18.23 (IOL_17A); also elsewhere on the board
F_DB7: U18.22 (IOL_14B); also elsewhere on the board
F_DB8: U18.21 (IOL_14A_GBIN6); also elsewhere on the board
F_DB9: U18.20 (IOL_13B_GBIN7); also elsewhere on the board
F_DB10: U18.19 (IOL_13A); also elsewhere on the board
F_DB11: U18.18 (IOL_12B); also elsewhere on the board
F_OFA: U18.1 (IOL_2A); also elsewhere on the board
F_OFB: U18.32 (IOL_24B); also elsewhere on the board
GND: C77.2, C82.2, C83.2, C84.2, C85.2, C86.2, C87.2, C88.2, C89.2, C90.2, C91.2, C92.2, C93.2, C94.2, C95.2, C96.2, C97.2, J4.8, U18.5 (GND), U18.13 (GND), U18.14 (GND), U18.53 (GNDPLL0), U18.59 (GND), U18.69 (GND), U18.86 (GND), U18.103 (GND), U18.127 (GNDPLL1), U18.132 (GND), U18.140 (GND), U19.4 (GND); also elsewhere on the board
GPIO0: U18.39 (IOB_61); also elsewhere on the board
GPIO1: U18.41 (IOB_63); also elsewhere on the board
GPIO2: U18.42 (IOB_64); also elsewhere on the board
GPIO3: U18.43 (IOB_71); also elsewhere on the board
LED_ARM: U18.37 (IOB_56); also elsewhere on the board
LED_TRIG: U18.38 (IOB_57); also elsewhere on the board
SD_A0: U18.121 (IOT_181); also elsewhere on the board
SD_A1: U18.120 (IOT_179); also elsewhere on the board
SD_A2: U18.119 (IOT_178); also elsewhere on the board
SD_A3: U18.118 (IOT_177); also elsewhere on the board
SD_A4: U18.117 (IOT_174); also elsewhere on the board
SD_A5: U18.116 (IOT_173); also elsewhere on the board
SD_A6: U18.115 (IOT_172); also elsewhere on the board
SD_A7: U18.114 (IOT_171); also elsewhere on the board
SD_A8: U18.113 (IOT_170); also elsewhere on the board
SD_A9: U18.112 (IOT_169); also elsewhere on the board
SD_A10: U18.122 (IOT_190); also elsewhere on the board
SD_A11: U18.110 (IOT_168); also elsewhere on the board
SD_BA0: U18.125 (IOT_192); also elsewhere on the board
SD_BA1: U18.124 (IOT_191); also elsewhere on the board
SD_CAS_N: U18.130 (IOT_206); also elsewhere on the board
SD_CKE: U18.107 (IOR_167); also elsewhere on the board
SD_CLK: U18.106 (IOR_166); also elsewhere on the board
SD_CS_N: U18.128 (IOT_197_GBIN1); also elsewhere on the board
SD_DQ0: U18.144 (IOT_222); also elsewhere on the board
SD_DQ1: U18.143 (IOT_221); also elsewhere on the board
SD_DQ2: U18.142 (IOT_220); also elsewhere on the board
SD_DQ3: U18.141 (IOT_219); also elsewhere on the board
SD_DQ4: U18.139 (IOT_217); also elsewhere on the board
SD_DQ5: U18.138 (IOT_216); also elsewhere on the board
SD_DQ6: U18.137 (IOT_215); also elsewhere on the board
SD_DQ7: U18.136 (IOT_214); also elsewhere on the board
SD_DQ8: U18.104 (IOR_164); also elsewhere on the board
SD_DQ9: U18.102 (IOR_161); also elsewhere on the board
SD_DQ10: U18.101 (IOR_160); also elsewhere on the board
SD_DQ11: U18.99 (IOR_152); also elsewhere on the board
SD_DQ12: U18.98 (IOR_148); also elsewhere on the board
SD_DQ13: U18.97 (IOR_147); also elsewhere on the board
SD_DQ14: U18.96 (IOR_146); also elsewhere on the board
SD_DQ15: U18.95 (IOR_144); also elsewhere on the board
SD_LDQM: U18.135 (IOT_213); also elsewhere on the board
SD_RAS_N: U18.129 (IOT_198_GBIN0); also elsewhere on the board
SD_UDQM: U18.105 (IOR_165); also elsewhere on the board
SD_WE_N: U18.134 (IOT_212); also elsewhere on the board
VCCPLL0: U18.54 (VCCPLL0); also elsewhere on the board
VCCPLL1: U18.126 (VCCPLL1); also elsewhere on the board

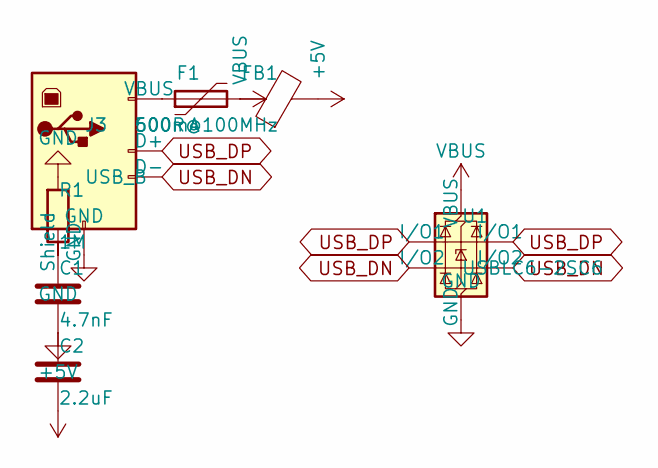
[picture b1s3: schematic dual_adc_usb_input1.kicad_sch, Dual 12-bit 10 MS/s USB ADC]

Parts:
C1: 4.7nF; C_0603_1608Metric
C2: 2.2uF; C_0603_1608Metric
F1: 500mA; Fuse_1206_3216Metric
FB1: 600R@100MHz; L_0805_2012Metric
J3: USB_B; USB_B_OST_USB-B1HSxx_Horizontal
R1: 1M; R_0603_1608Metric
U1: USBLC6-2SC6; SOT-23-6

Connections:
+5V: C2.1, FB1.2; also elsewhere on the board
GND: C1.2, C2.2, J3.4 (GND), R1.2, U1.2 (GND); also elsewhere on the board
unnamed: C1.1, J3.SH (Shield), R1.1
unnamed: F1.1, J3.1 (VBUS)
USB_DN: J3.2 (D-), U1.3 (I/O2), U1.4 (I/O2); also elsewhere on the board
USB_DP: J3.3 (D+), U1.1 (I/O1), U1.6 (I/O1); also elsewhere on the board
VBUS: F1.2, FB1.1, U1.5 (VBUS)

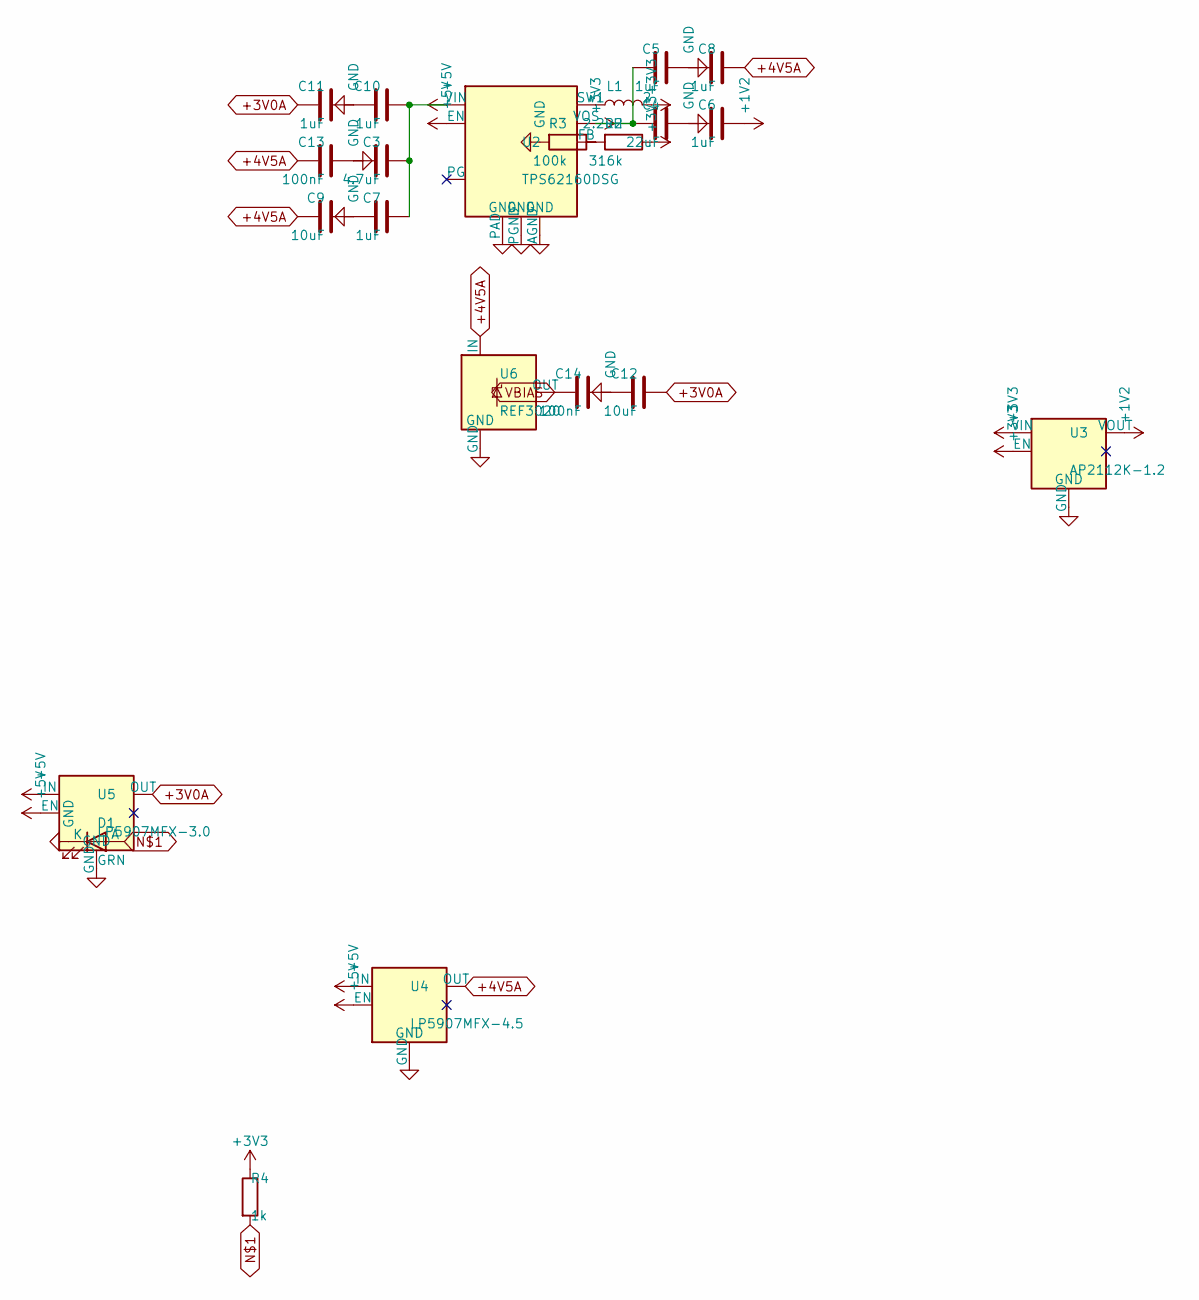
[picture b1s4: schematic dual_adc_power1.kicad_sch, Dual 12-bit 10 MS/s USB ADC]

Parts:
C3: 4.7uF; C_0805_2012Metric
C4: 22uF; C_0805_2012Metric
C5, C6, C7, C8, C10, C11: 1uF; C_0603_1608Metric
C9, C12: 10uF; C_0805_2012Metric
C13, C14: 100nF; C_0402_1005Metric
D1: GRN; LED_0603_1608Metric
L1: 2.2uH; L_Changjiang_FNR3015S
R2: 316k; R_0603_1608Metric
R3: 100k; R_0603_1608Metric
R4: 1k; R_0603_1608Metric
U2: TPS62160DSG; WSON-8-1EP_2x2mm_P0.5mm_EP0.9x1.6mm_ThermalVias
U3: AP2112K-1.2; SOT-23-5
U4: LP5907MFX-4.5; SOT-23-5
U5: LP5907MFX-3.0; SOT-23-5
U6: REF3020; SOT-23

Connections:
+1V2: C6.1, U3.5 (VOUT); also elsewhere on the board
+3V3: C4.1, C5.1, L1.2, R2.1, R4.1, U2.6 (VOS), U3.1 (VIN), U3.3 (EN); also elsewhere on the board
+4V5A: C8.1, C9.1, C13.1, U4.5 (OUT), U6.1 (IN); also elsewhere on the board
+5V: C3.1, C7.1, C10.1, U2.2 (VIN), U2.3 (EN), U4.1 (IN), U4.3 (EN), U5.1 (IN), U5.3 (EN); also elsewhere on the board
GND: C3.2, C4.2, C5.2, C6.2, C7.2, C8.2, C9.2, C10.2, C11.2, C12.2, C13.2, C14.2, D1.1 (K), R3.2, U2.1 (PGND), U2.4 (AGND), U2.9 (PAD), U3.2 (GND), U4.2 (GND), U5.2 (GND), U6.3 (GND); also elsewhere on the board
unnamed: D1.2 (A), R4.2
unnamed: R2.2, R3.1, U2.5 (FB)
unnamed: L1.1, U2.7 (SW)
VBIAS: C14.1, U6.2 (OUT); also elsewhere on the board
